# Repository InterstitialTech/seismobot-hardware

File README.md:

# seismobot-hardware
Geophone DAQ board: KiCad project files

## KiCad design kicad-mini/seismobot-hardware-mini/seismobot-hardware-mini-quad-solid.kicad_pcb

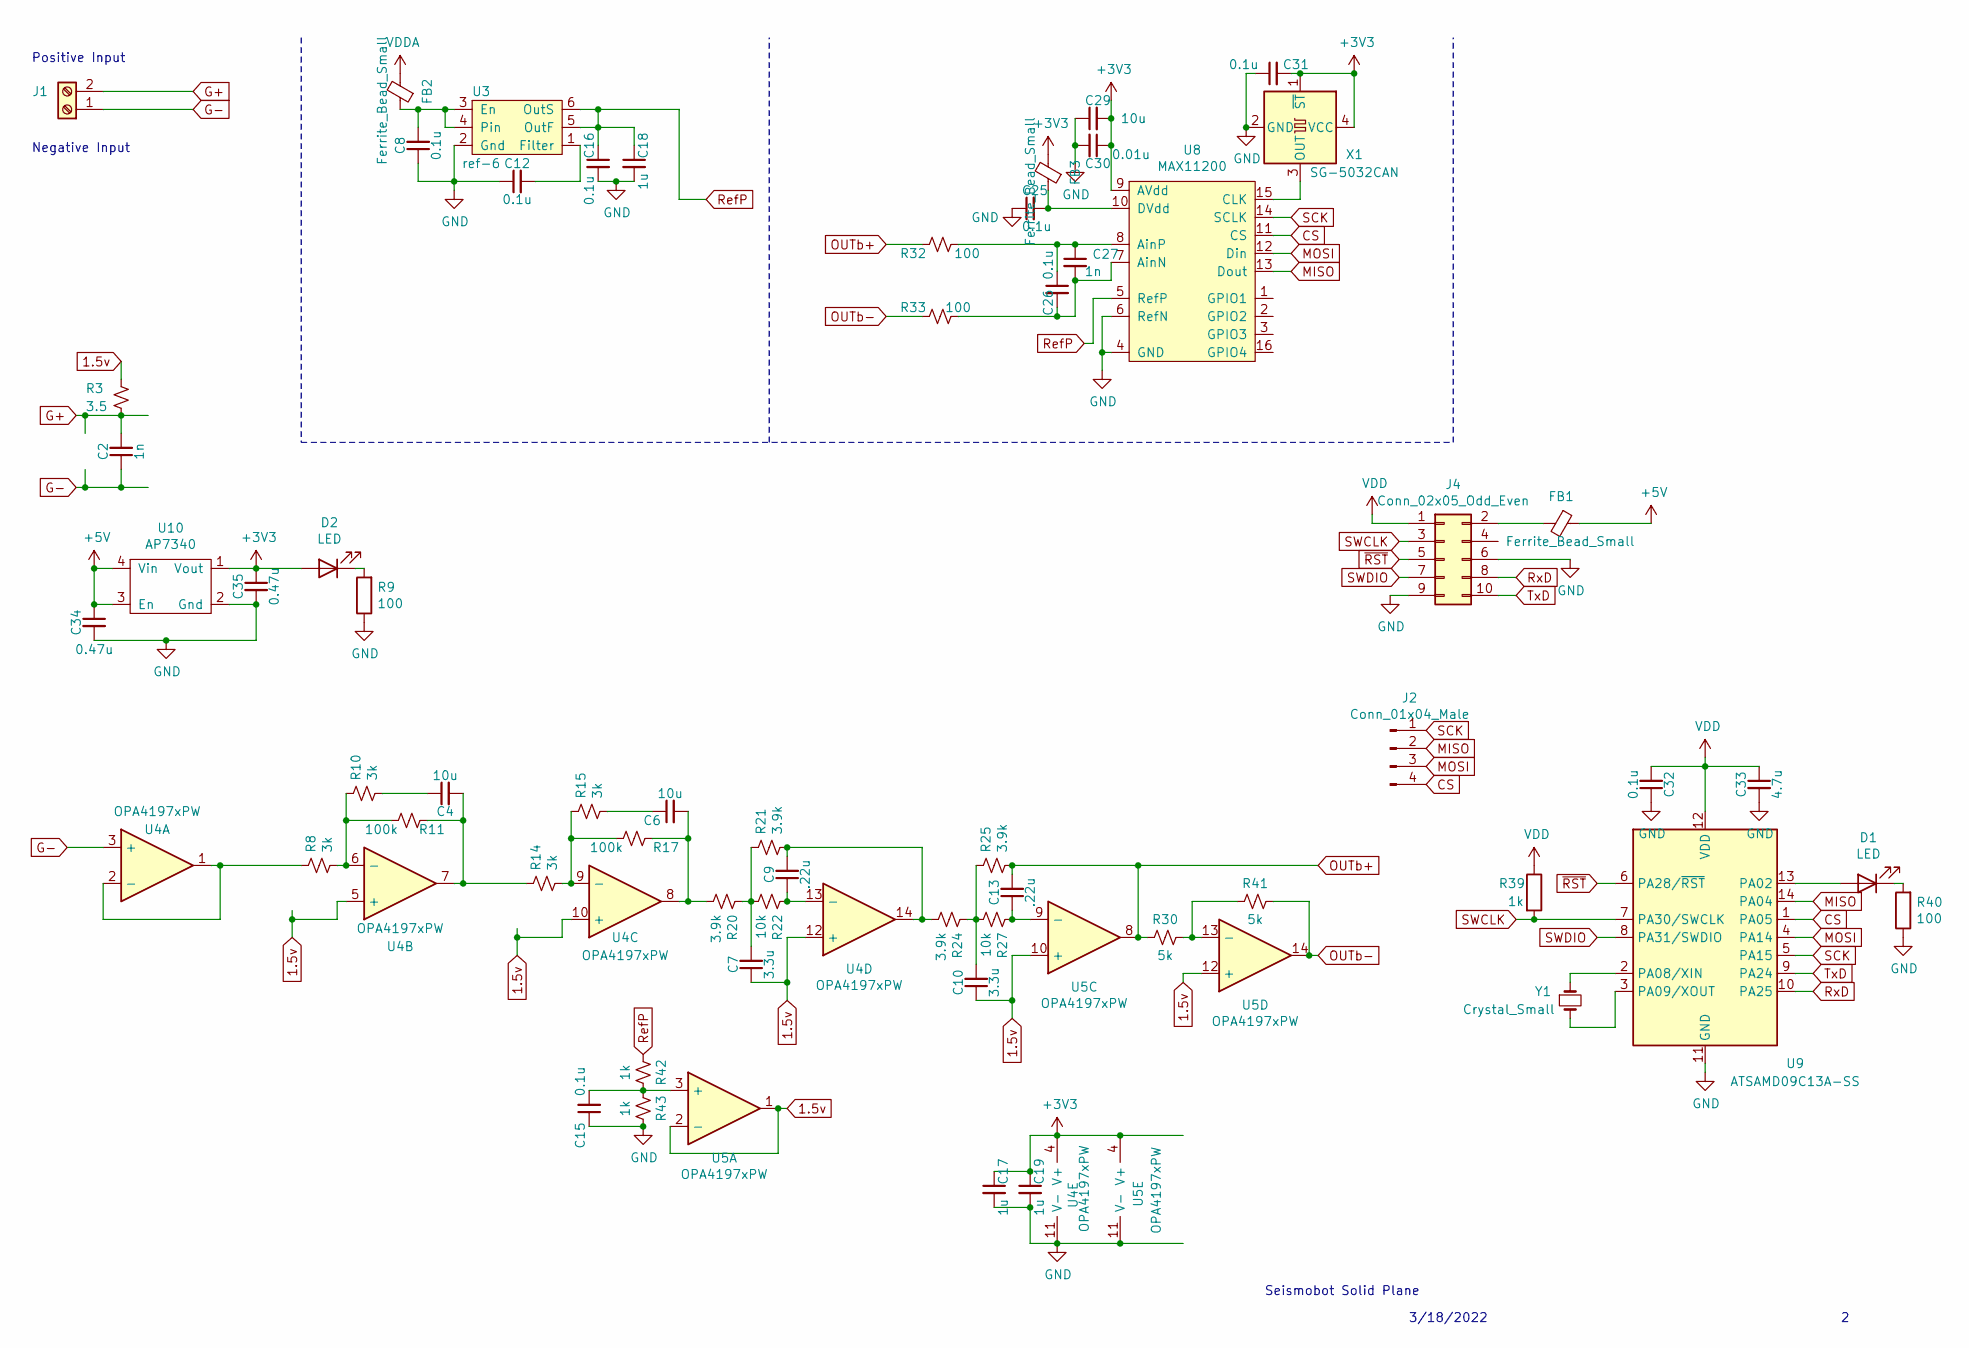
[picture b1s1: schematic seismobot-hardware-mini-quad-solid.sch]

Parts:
C2, C27: 1n; C_0805_2012Metric
C4, C6, C29: 10u; C_1206_3216Metric
C7, C10: 3.3u; C_0805_2012Metric
C8, C12, C15, C16, C25, C26, C31, C32: 0.1u; C_0805_2012Metric
C9, C13: .22u; C_0805_2012Metric
C17, C18, C19: 1u; C_0805_2012Metric
C30: 0.01u; C_0805_2012Metric
C33: 4.7u; C_0805_2012Metric
C34, C35: 0.47u; C_0805_2012Metric
D1, D2: LED; LED_0805_2012Metric
FB1, FB2, FB3: Ferrite_Bead_Small; R_0805_2012Metric
J1: Screw_Terminal_01x02; PhoenixContact_MCV_1,5_2-G-3.5_1x02_P3.50mm_Vertical
J2: Conn_01x04_Male; PinHeader_1x04_P1.27mm_Vertical
J4: Conn_02x05_Odd_Even; PinSocket_2x05_P2.54mm_Vertical
R3: 3.5; R_1206_3216Metric
R8, R10, R14, R15: 3k; R_0805_2012Metric
R9, R32, R33, R40: 100; R_0805_2012Metric
R11, R17: 100k; R_0805_2012Metric
R20, R21, R24, R25: 3.9k; R_0805_2012Metric
R22, R27: 10k; R_0805_2012Metric
R30, R41: 5k; R_0805_2012Metric
R39, R42, R43: 1k; R_0805_2012Metric
U3: ref-6; SOT-23-6
U4, U5: OPA4197xPW; SOIC-14_3.9x8.7mm_P1.27mm
U8: MAX11200; QSOP-16
U9: ATSAMD09C13A-SS; SOIC-14_3.9x8.7mm_P1.27mm
U10: AP7340; DFN-1010-4
X1: SG-5032CAN; Oscillator_SMD_SeikoEpson_SG8002LB-4Pin_5.0x3.2mm
Y1: Crystal_Small; Crystal_SMD_3215-2Pin_3.2x1.5mm

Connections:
1.5v: C7.1, C10.1, R3.1, U4.5 (+), U4.10 (+), U4.12 (+), U5.1, U5.2 (-), U5.10 (+), U5.12 (+)
+5V: C34.1, FB1.1, U10.3 (En), U10.4 (Vin)
CS: J2.4, U8.11 (CS), U9.1 (PA05)
G+: C2.2, J1.2, R3.2
G-: C2.1, J1.1, U4.3 (+)
GND: C8.1, C12.1, C15.1, C16.2, C17.2, C18.2, C19.2, C25.1, C29.1, C30.2, C31.1, C32.1, C33.2, C34.2, C35.2, J4.6, J4.9, R9.1, R40.1, R43.1, U3.2 (Gnd), U4.11 (V-), U5.11 (V-), U8.4 (GND), U8.6 (RefN), U9.11 (GND), U10.2 (Gnd), X1.2 (GND); also elsewhere on the board
MISO: J2.2, U8.13 (Dout), U9.14 (PA04)
MOSI: J2.3, U8.12 (Din), U9.4 (PA14)
unnamed: C4.1, R10.2
unnamed: C4.2, R11.1, R14.1, U4.7
unnamed: C6.1, R15.2
unnamed: C6.2, R17.1, R20.2, U4.8
unnamed: C7.2, R20.1, R21.1, R22.2
unnamed: C8.2, FB2.1, U3.3 (En), U3.4
unnamed: C9.1, R22.1, U4.13 (-)
unnamed: C9.2, R21.2, R24.2, U4.14
unnamed: C10.2, R24.1, R25.1, R27.2
unnamed: C12.2, U3.1 (Filter)
unnamed: C13.1, R27.1, U5.9 (-)
unnamed: C15.2, R42.1, R43.2, U5.3 (+)
unnamed: C26.1, C27.1, R32.1, U8.8 (AinP)
unnamed: C26.2, C27.2, R33.1, U8.7 (AinN)
unnamed: D1.1 (K), R40.2
unnamed: D1.2 (A), U9.13 (PA02)
unnamed: D2.1 (K), R9.2
unnamed: FB1.2, J4.2
unnamed: R8.1, U4.1, U4.2 (-)
unnamed: R8.2, R10.1, R11.2, U4.6 (-)
unnamed: R14.2, R15.1, R17.2, U4.9 (-)
unnamed: R30.1, R41.2, U5.13 (-)
unnamed: U8.15 (CLK), X1.3 (OUT)
unnamed: U9.2 (PA08/XIN), Y1.1
unnamed: U9.3 (PA09/XOUT), Y1.2
OUTb+: C13.2, R25.2, R30.2, R32.2, U5.8
OUTb-: R33.2, R41.1, U5.14
RefP: C16.1, C18.1, R42.2, U3.5 (OutF), U3.6 (OutS), U8.5 (RefP)
RxD: J4.8, U9.10 (PA25)
SCK: J2.1, U8.14 (SCLK), U9.5 (PA15)
SWCLK: J4.3, R39.2, U9.7 (PA30/SWCLK)
SWDIO: J4.7, U9.8 (PA31/SWDIO)
TxD: J4.10, U9.9 (PA24)
VDD: C32.2, C33.1, J4.1, R39.1, U9.12 (VDD); also elsewhere on the board
~RST: J4.5, U9.6 (PA28/~RST)

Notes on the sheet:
Negative Input
Positive Input
Seismobot Solid Plane
3/18/2022

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
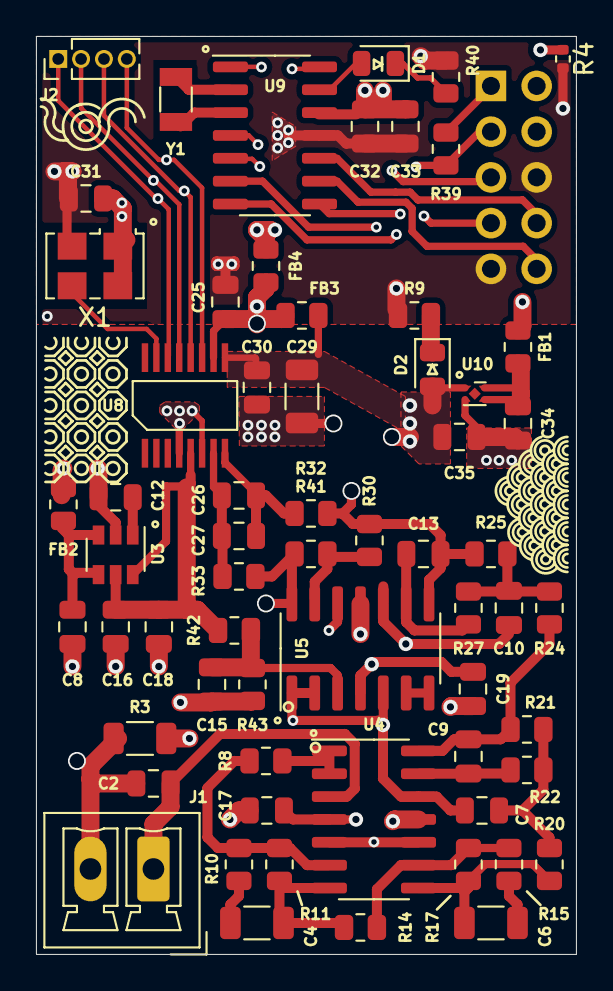
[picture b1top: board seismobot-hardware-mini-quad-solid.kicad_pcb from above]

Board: 4 copper layers, 30.0 x 51.0 mm, 64 parts (1 on the bottom side), 45 nets.

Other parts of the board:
FB4: 0; R_0805_2012Metric
R4: 0; R_0402_1005Metric

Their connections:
GND: R4.2; also elsewhere on the board
VDD: FB4.1; also elsewhere on the board

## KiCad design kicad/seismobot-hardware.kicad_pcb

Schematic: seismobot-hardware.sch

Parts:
C1, C8, C9, C12, C13, C16, C17, C25, C26, C31, C32: 0.1u; C_0805_2012Metric
C2, C4, C27: 1n; C_0805_2012Metric
C3, C11: 3.3u; C_0805_2012Metric
C5, C14: .22u; C_0805_2012Metric
C6, C7, C10, C21, C28, C29: 10u; C_1206_3216Metric
C15: 10n; C_0805_2012Metric
C18, C19, C36, C37, C38, C39, C40: 1u; C_0805_2012Metric
C20, C22: 2u; C_0805_2012Metric
C23, C24: DNP; C_0805_2012Metric
C30: 0.01u; C_0805_2012Metric
C33: 4.7u; C_0805_2012Metric
C34, C35: 0.47u; C_0805_2012Metric
D1, D2: LED; LED_0805_2012Metric
J1: Screw_Terminal_01x02; PhoenixContact_MCV_1,5_2-G-3.5_1x02_P3.50mm_Vertical
J2: Raspberry_Pi_2_3; PinHeader_2x20_P2.54mm_Vertical
J3: Conn_01x06_Male; PinHeader_1x06_P2.54mm_Horizontal
JP1, JP2: Jumper_2_Open; PinHeader_1x02_P2.54mm_Vertical
JP3, JP4, JP5: Jumper_NC_Dual; PinHeader_1x03_P2.54mm_Vertical
R1, R2, R26, R34, R39: 1k; R_0805_2012Metric
R3: 3.5; R_1206_3216Metric
R4, R6, R16, R18: 3.9k; R_0805_2012Metric
R5: 200; R_0805_2012Metric
R7, R19: 10k; R_0805_2012Metric
R8, R15: 21; R_0805_2012Metric
R9, R32, R33, R40: 100; R_0805_2012Metric
R10, R13: 0; R_0805_2012Metric
R11, R12: 32.88k; R_0805_2012Metric
R14: DNP; R_0805_2012Metric
R17: 99k; R_0805_2012Metric
R20: 5; R_0805_2012Metric
R21: 150k; R_0805_2012Metric
R22: 4k; R_0805_2012Metric
R23, R31: 2k; R_0805_2012Metric
R25, R27, R37, R38: 5k; R_0805_2012Metric
R28, R35: 3k; R_0805_2012Metric
R29, R36: 100k; R_0805_2012Metric
TP1, TP2: TestPoint; PinHeader_1x01_P2.54mm_Vertical
U1, U2, U6, U7: OPA2156xD; SOIC-8_3.9x4.9mm_P1.27mm
U3: ref-6; SOT-23-6
U4: ref-8; SOIC-8_3.9x4.9mm_P1.27mm
U5: LTC6011; SOIC-8_3.9x4.9mm_P1.27mm
U8: MAX11200; QSOP-16
U9: ATSAMD09C13A-SS; SOIC-14_3.9x8.7mm_P1.27mm
U10: AP7340; DFN-1010-4
X1: SG-5032CAN; Oscillator_SMD_SeikoEpson_SG8002LB-4Pin_5.0x3.2mm
Y1: Crystal; Crystal_SMD_Suntsu_SWS83412D16-4Pin_8.0x3.8mm

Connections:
1.5v: C3.1, C11.1, C20.1, C22.1, R3.1, R20.2, U1.3, U2.6, U2.7, U5.3, U6.3, U6.5, U7.3, U7.5
+3V3: C25.2, C29.2, C30.1, C31.2, C35.1, C36.1, C37.1, C38.1, C39.1, C40.1, D2.2 (A), R10.1, R13.1, U1.8, U2.8, U5.8, U6.8, U7.8, U8.9 (AVdd), U8.10 (DVdd), U10.1 (Vout), X1.1 (~ST), X1.4 (VCC)
+5V: C34.1, J2.2 (5V), U10.3 (En), U10.4 (Vin)
CS: U8.11 (CS), U9.1 (PA05)
G+: C2.2, J1.2, JP1.1 (A), R3.2, R14.2
G-: C2.1, J1.1, JP2.1 (A), R14.1, U1.5
GND: C1.1, C8.1, C9.1, C12.1, C13.1, C16.2, C17.2, C18.2, C19.2, C23.2, C24.1, C25.1, C29.1, C30.2, C31.1, C32.1, C33.2, C34.2, C35.2, C36.2, C37.2, C38.2, C39.2, C40.2, J2.6 (GND), J2.9 (GND), J2.14 (GND), J2.20 (GND), J2.25 (GND), J2.30 (GND), J2.34 (GND), J2.39 (GND), J3.3, J3.6, R2.1, R9.1, R22.1, R40.1, TP1.1, TP2.1, U1.4, U2.4, U3.2 (Gnd), U4.3 (Gnd), U4.4 (GndS), U5.4, U6.4, U7.4, U8.4 (GND), U8.6 (RefN), U9.11 (GND), U10.2 (Gnd), X1.2 (GND)
MISO: U8.13 (Dout), U9.14 (PA04)
MOSI: U8.12 (Din), U9.4 (PA14)
unnamed: C1.2, R1.1, R2.2, U2.5
unnamed: C3.2, R4.1, R6.1, R7.2
unnamed: C4.1, JP1.2 (B), R5.2
unnamed: C4.2, R5.1, R8.2, R11.2, U2.3
unnamed: C5.1, R7.1, U1.2
unnamed: C5.2, R6.2, R16.2, U1.1
unnamed: C6.1, R15.1
unnamed: C6.2, JP2.2 (B), R12.1, U2.2
unnamed: C7.1, R8.1
unnamed: C8.2, R13.2, U3.3 (En), U3.4
unnamed: C9.2, R10.2, U4.2 (Vin)
unnamed: C7.2, C10.1, R11.1, R12.2, R15.2, U2.1
unnamed: C10.2, R17.2
unnamed: C11.2, R16.1, R18.1, R19.2
unnamed: C12.2, U3.1 (Filter)
unnamed: C13.2, U4.1 (NR)
unnamed: C14.1, R19.1, U6.6
unnamed: C14.2, R18.2, R23.1, U6.7
unnamed: C15.1, R17.1, R21.2, U5.2
unnamed: C16.1, C18.1, JP3.3, U3.5 (OutF), U3.6 (OutS)
unnamed: C17.1, C19.1, JP3.1, U4.6 (OutS), U4.7 (OutF)
unnamed: C20.2, R23.2, R26.1
unnamed: C21.1, R28.2
unnamed: C21.2, R29.1, R31.1, U6.1
unnamed: C22.2, R31.2, R34.1
unnamed: C23.1, C26.1, C27.1, R32.1, U8.8 (AinP)
unnamed: C24.2, C26.2, C27.2, R33.1, U8.7 (AinN)
unnamed: C28.1, R35.2
unnamed: D1.1 (K), R40.2
unnamed: D1.2 (A), U9.13 (PA02)
unnamed: D2.1 (K), R9.2
unnamed: JP4.2, R32.2
unnamed: JP5.2, R33.2
unnamed: R4.2, U1.6, U1.7
unnamed: R20.1, R22.2, U5.5
unnamed: R25.1, R27.2, U5.6
unnamed: R26.2, R28.1, R29.2, U6.2
unnamed: R34.2, R35.1, R36.2, U7.2
unnamed: R37.1, R38.2, U7.6
unnamed: U8.15 (CLK), X1.3 (OUT)
unnamed: U9.2 (PA08/XIN), Y1.1
unnamed: U9.3 (PA09/XOUT), Y1.4
OUTa+: JP4.1, R27.1, U5.7
OUTa-: C15.2, JP5.3, R21.1, R25.2, U5.1
OUTb+: C28.2, JP4.3, R36.1, R37.2, U7.1
OUTb-: JP5.1, R38.1, U7.7
RefP: JP3.2, R1.2, U8.5 (RefP)
RxD: J2.8 (GPIO14/TXD), U9.10 (PA25)
SCK: U8.14 (SCLK), U9.5 (PA15)
SWCLK: J3.2, R39.2, U9.7 (PA30/SWCLK)
SWDIO: J3.4, U9.8 (PA31/SWDIO)
TxD: J2.10 (GPIO15/RXD), U9.9 (PA24)
VDD: C32.2, C33.1, J2.1 (3V3), J3.1, R39.1, U9.12 (VDD)
~RST: J3.5, U9.6 (PA28/~RST)

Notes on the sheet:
Negative Input
Positive Input

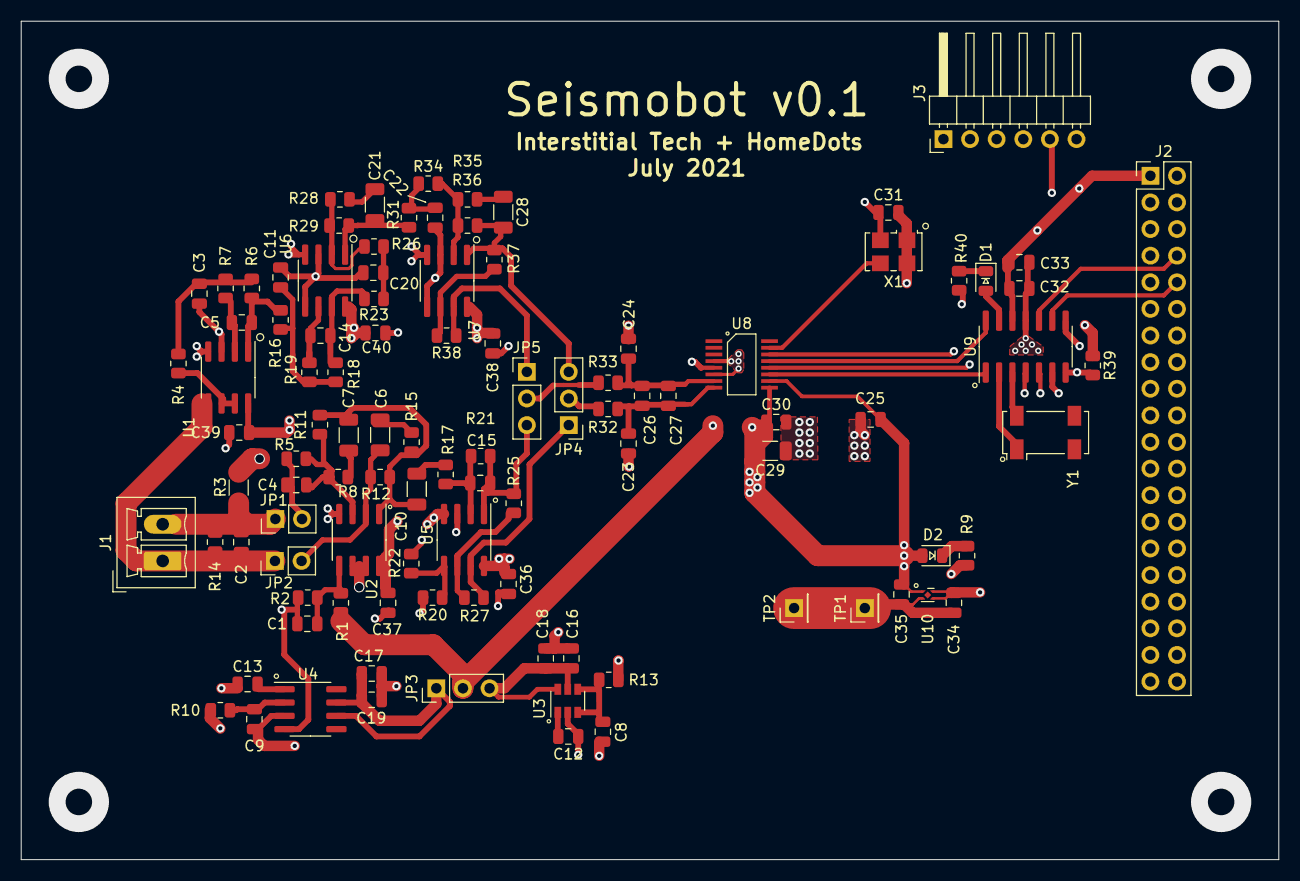
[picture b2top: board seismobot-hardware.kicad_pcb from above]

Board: 4 copper layers, 120.0 x 80.0 mm, 102 parts (0 on the bottom side), 63 nets.

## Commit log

2021-04-29 README.md: update project name
2021-04-29 add bom.csv
2021-04-30 bom.csv: change from 26 to 40 pin header
2021-05-05 Create .gitignore
    adding .gitignore
2021-05-05 added kicad project
2021-05-05 added max11200 to new library
2021-05-05 raspberry pi header and mcu on schematic
2021-05-19 add MCU (ATSAMD09) and supporting circuitry
2021-05-21 Added passives and clock to ADC
    Based off of dev board
2021-05-21 started noise calculations
2021-05-22 added noise analysis
2021-05-22 added voltage reference symbols
2021-05-22 added voltage references to schematic
2021-05-23 add input stage 1
2021-06-14 Cleaned things up, add new signal path
    added a new 6-pole, 2-zero filter
2021-06-14 add jumpers for signal path selection
2021-06-14 add footprints to all components
2021-06-16 add v1 signal path routing
2021-06-16 add v2 signal path routing
2021-06-27 add 3v3 regulator, simplify signal split, add planes
2021-06-30 add 3v3 regulator, more routing
2021-06-30 add 3v3 power led
2021-06-30 resize board
2021-07-24 finishing touches before sending out rev 1
2021-07-24 add BOM
2021-07-24 add v1 gerbers
2021-08-23 re-arrange schematic for aesthetics, add Title Block
2021-08-23 sym-lib-table, cache and rescue files for kicad v5.1.5
2021-08-23 README: add schematic
2021-11-17 adding opa388 submodule for simulation
2021-11-17 not sure what changed here, sorry
2021-11-17 cleaning things up
2021-11-17 playing with more numbers
2021-12-07 add LICENSE
2022-04-04 add mini-quad-solid
